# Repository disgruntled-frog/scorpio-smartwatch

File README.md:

# scorpio-smartwatch
Open sourced smartwatch designed to track activities, and key biometrics. Includes GPS, motion sensors, heart rate and BLE. No subscription, no cloud.

### Component Breakdown (Subject to Change)
- MCU: NRF52840
- GPS: MIA-M10Q
- IMU: LSM6DSV80X
- MAG: LIS2MDL
- FLASH: ZDSD16GLGIAG
- SCREEN: (TBD) LPM010M297B
     - Appears to be the same screen specs as Garmin Forerunner 45

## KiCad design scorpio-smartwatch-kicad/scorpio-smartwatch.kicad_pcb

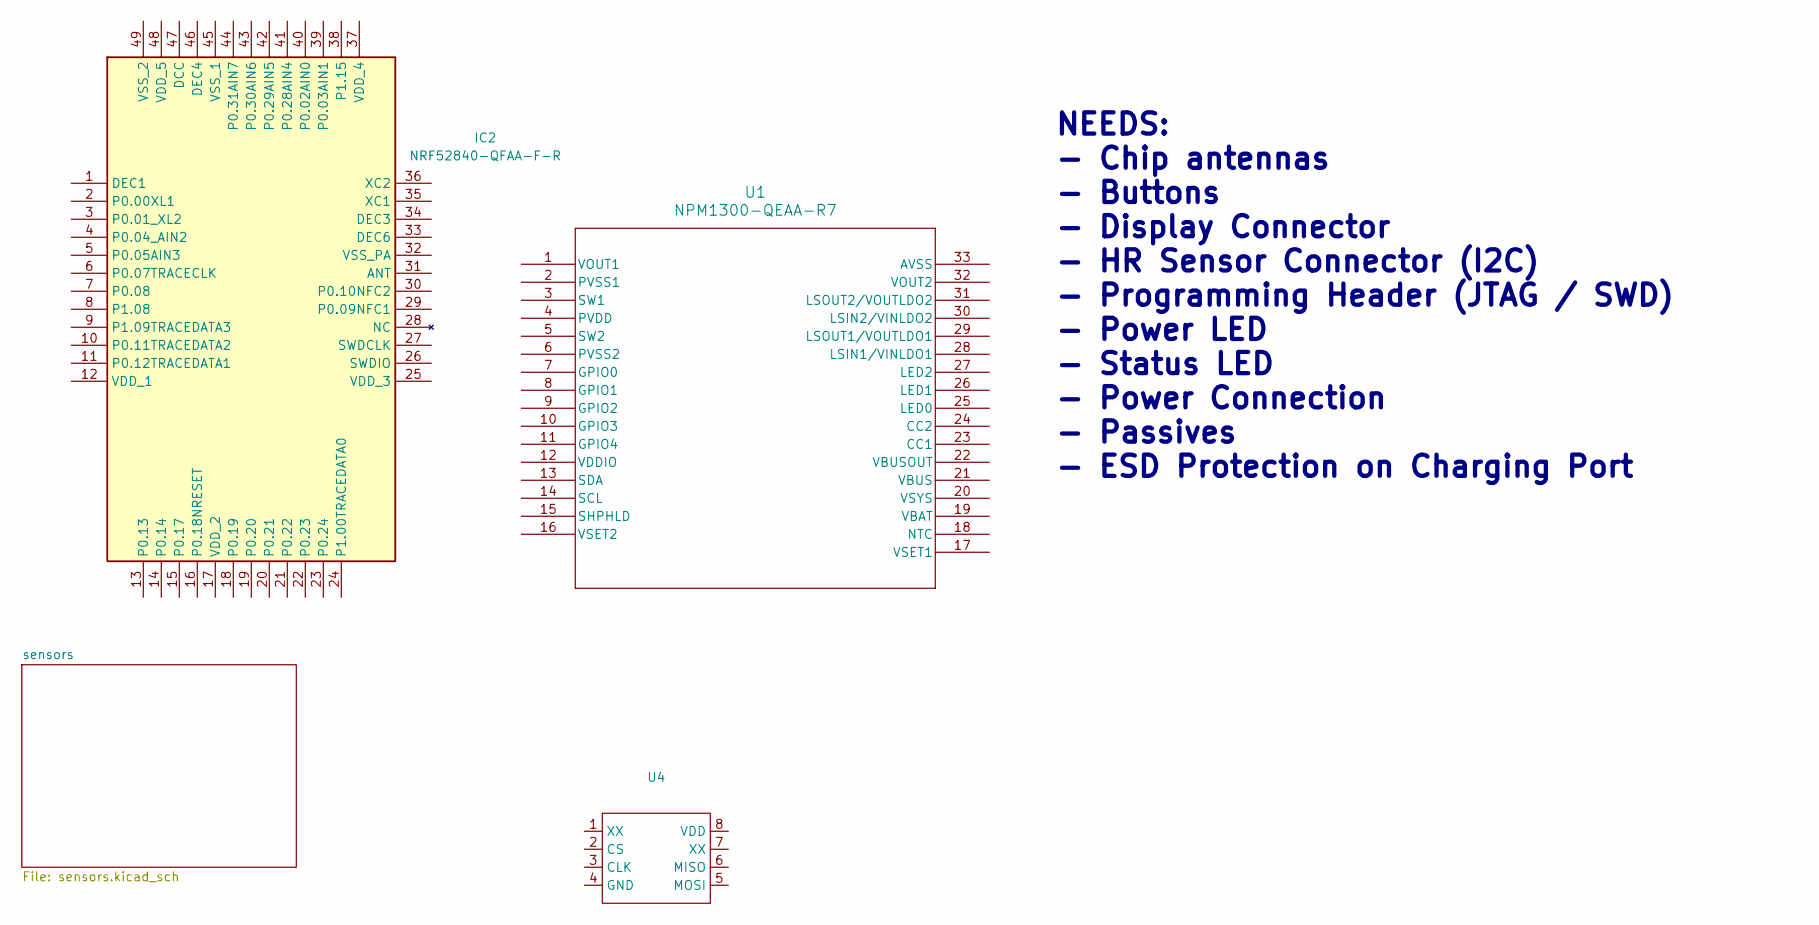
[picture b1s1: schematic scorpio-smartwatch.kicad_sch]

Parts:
IC2: NRF52840-QFAA-F-R; QFN40P600X600X95-49N-D; Mouser Part Number 949-NRF52840QFAA-R
U1: NPM1300-QEAA-R7; QFN32_5X5_NOR-M
U4: LGA-8_8x6.2mm_P1.27mm

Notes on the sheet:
NEEDS: - Chip antennas - Buttons - Display Connector - HR Sensor Connector (I2C) - Programming Header (JTAG / SWD) - Power LED - Status LED - Power Connection - Passives - ESD Protection on Charging Port

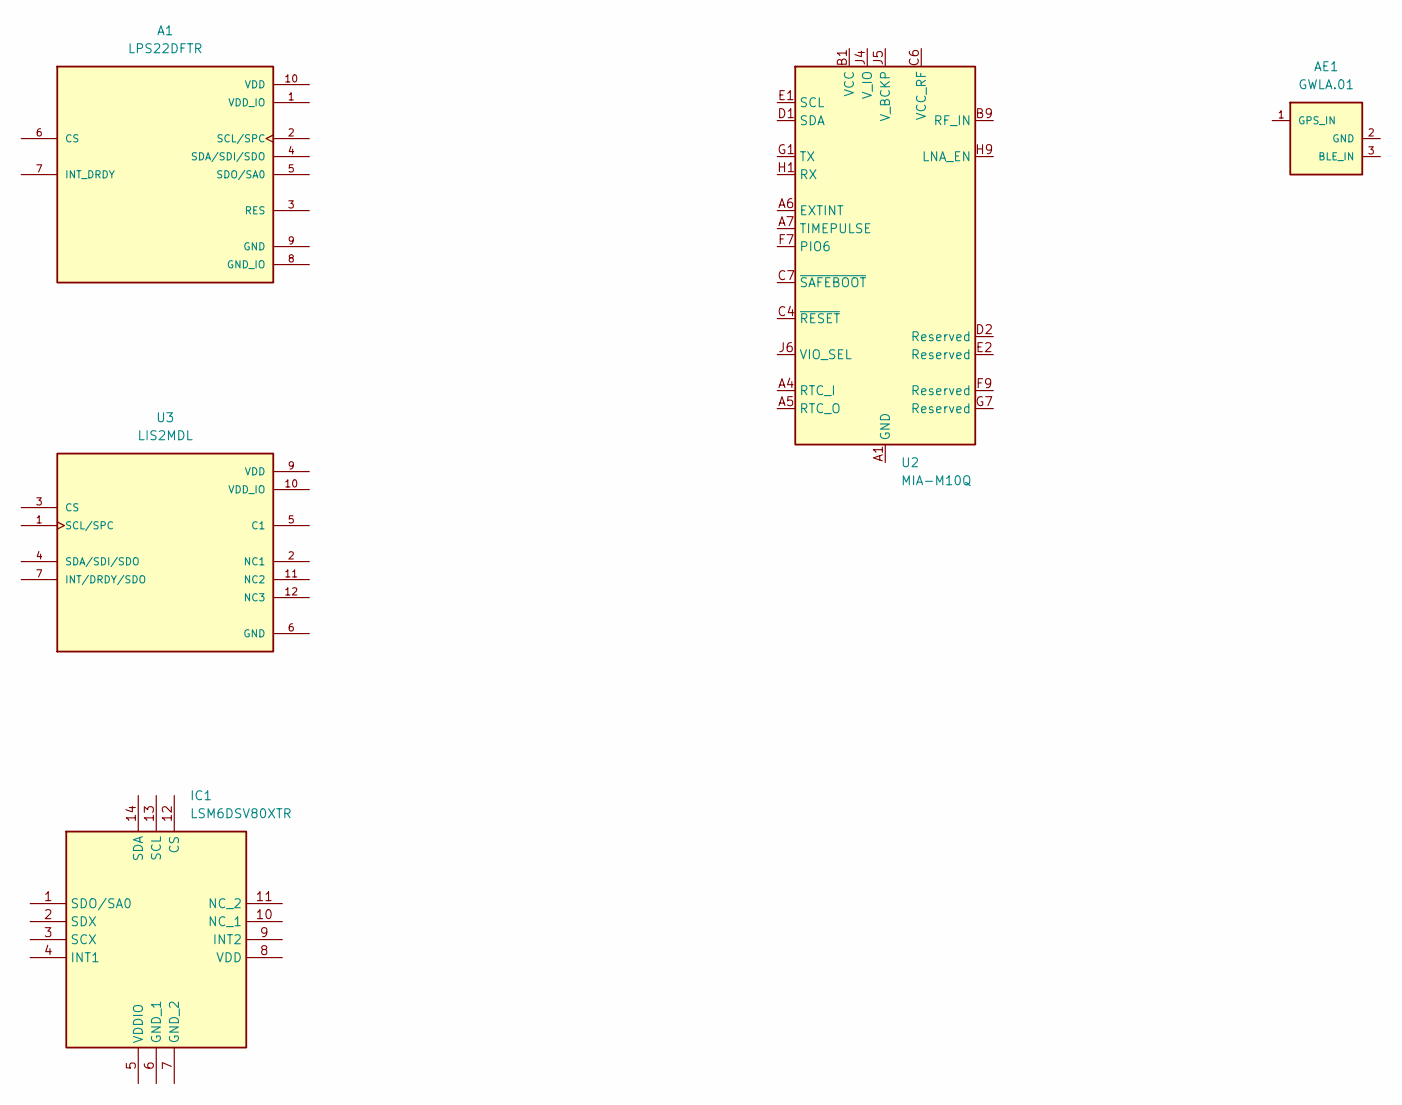
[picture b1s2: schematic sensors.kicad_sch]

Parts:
A1: LPS22DFTR; XDCR_LPS22DFTR; PARTREV 3
AE1: GWLA.01; TOAGLAS_GWLA.01
IC1: LSM6DSV80XTR; LSM6DSV16BXTR; Manufacturer_Part_Number LSM6DSV80XTR
U2: MIA-M10Q; ublox_LGA-53_4.5x4.5mm_Layout9x9_P0.5mm
U3: LIS2MDL; PQFN50P200X200X70-12N; PARTREV Rev 5

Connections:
GND: U3.6 (GND), U3.8 (GND)
unnamed: U2.A1 (GND), U2.A2 (GND), U2.A3 (GND), U2.A8 (GND), U2.A9 (GND), U2.B2 (GND), U2.B8 (GND), U2.C3 (GND), U2.C9 (GND), U2.E3 (GND), U2.E4 (GND), U2.E9 (GND), U2.F1 (GND), U2.F3 (GND), U2.F4 (GND), U2.G3 (GND), U2.G4 (GND), U2.G5 (GND), U2.G6 (GND), U2.H8 (GND), U2.J8 (GND), U2.J9 (GND)

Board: 2 copper layers, 8 parts (0 on the bottom side), 2 nets, no tracks yet.

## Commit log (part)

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2026-05-23 init commit for kicad, adding sensors and mcu for first rough idea
2026-05-24 Adding dimensions on the pcb and adding tables for current and battery sizes. need to change NRF footprint still. Need to add: Buttons, Screen Connector / Driver, HR connector (I2C), Power Management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
2026-05-24 minor changes
2026-05-27 wip commit, added chip antenna, trying out different pcb sizes. not routing until we can figure out the rf nightmare with ground plane sizes.
